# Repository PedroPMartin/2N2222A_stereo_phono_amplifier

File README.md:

2N2222A Stereo Phono Amplifier
=======
Based on [Hans Polak and Ivey's](https://www.diyaudio.com/community/threads/2n2222a-phono-preamp.158918/post-6392737) design. <br>
Thanks for Hans Polak and Ivey.

This design is similar but uses LM317 and no Zener diode

BOM <br>
Reference(s): Value <br>
C1, C2, C8, C9, C101, C102: 330uF /50V <br>
C3, C103	6n8 <br>
C4, C104	22n <br>
C5, C7, C105:	47uF / 50V <br>
C6, C106:	1uF/50V non electrolytic <br>
C11,C111: 3p3 <br>
J1, J3	TerminalBlock:TerminalBlock_bornier-3_P5.08mm  <br>
J2	TerminalBlock:TerminalBlock_bornier-2_P5.08mm  <br>
Q1, Q2, Q3, Q101, Q102, Q103:	2N2222A <br>
R1, R101:	150 Ohm <br>
R2, R9, R102, R109:	1K8 <br>
R3, R103:	8K2 <br>
R4, R8, R104, R108:	100 <br>
R5, R105:	12K <br>
R6, R106:	270K <br>
R7, R107:	6K <br>
R10, R110:	1K <br>
R12, R112:	47K <br>
R13, R113:	4K7 <br>
R14, R114:	10K <br>
R11: 220 <br>
R15:	3K3  <br>
U1:	LM317_TO-220 <cr>

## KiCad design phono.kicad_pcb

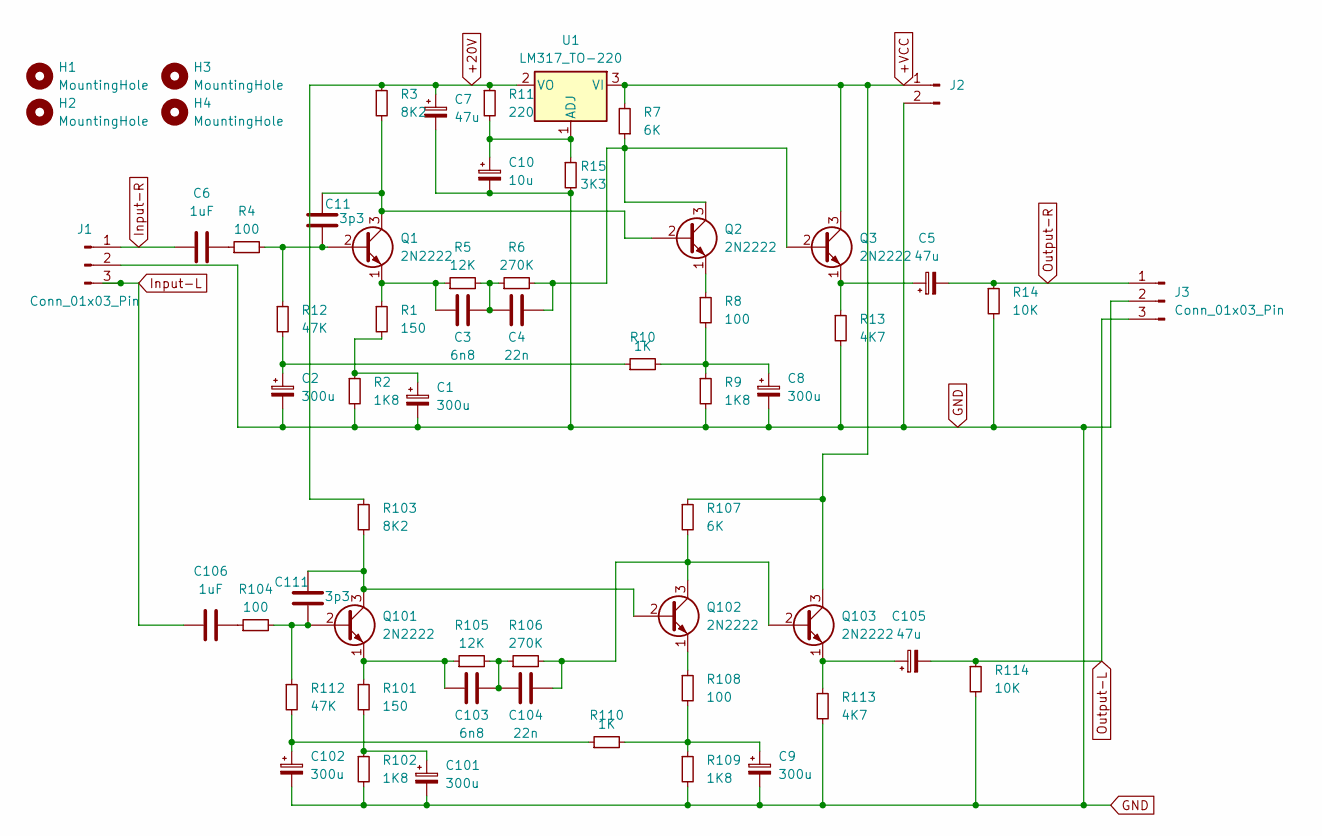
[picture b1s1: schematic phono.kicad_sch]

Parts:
C1, C2, C8, C9, C101, C102: 300u; CP_Radial_D10.0mm_P5.00mm
C3, C103: 6n8; C_Axial_L3.8mm_D2.6mm_P10.00mm_Horizontal
C4, C104: 22n; C_Axial_L3.8mm_D2.6mm_P10.00mm_Horizontal
C5, C7, C105: 47u; CP_Radial_D10.0mm_P5.00mm
C6, C106: 1uF; C_Axial_L3.8mm_D2.6mm_P10.00mm_Horizontal
C10: 10u; CP_Radial_D5.0mm_P2.00mm
C11, C111: 3p3; C_Disc_D3.0mm_W2.0mm_P2.50mm
H1, H2, H3, H4: MountingHole; MountingHole_3.2mm_M3
J1, J3: Conn_01x03_Pin; TerminalBlock_bornier-3_P5.08mm
J2: Conn_01x02_Pin; TerminalBlock_bornier-2_P5.08mm
Q1, Q2, Q3, Q101, Q102, Q103: 2N2222; TO-39-3
R1, R101: 150; R_Axial_DIN0207_L6.3mm_D2.5mm_P10.16mm_Horizontal
R2, R9, R102, R109: 1K8; R_Axial_DIN0207_L6.3mm_D2.5mm_P10.16mm_Horizontal
R3, R103: 8K2; R_Axial_DIN0207_L6.3mm_D2.5mm_P10.16mm_Horizontal
R4, R8, R104, R108: 100; R_Axial_DIN0207_L6.3mm_D2.5mm_P10.16mm_Horizontal
R5, R105: 12K; R_Axial_DIN0207_L6.3mm_D2.5mm_P10.16mm_Horizontal
R6, R106: 270K; R_Axial_DIN0207_L6.3mm_D2.5mm_P10.16mm_Horizontal
R7, R107: 6K; R_Axial_DIN0207_L6.3mm_D2.5mm_P10.16mm_Horizontal
R10, R110: 1K; R_Axial_DIN0207_L6.3mm_D2.5mm_P10.16mm_Horizontal
R11: 220; R_Axial_DIN0207_L6.3mm_D2.5mm_P10.16mm_Horizontal
R12, R112: 47K; R_Axial_DIN0207_L6.3mm_D2.5mm_P10.16mm_Horizontal
R13, R113: 4K7; R_Axial_DIN0207_L6.3mm_D2.5mm_P10.16mm_Horizontal
R14, R114: 10K; R_Axial_DIN0207_L6.3mm_D2.5mm_P10.16mm_Horizontal
R15: 3K3; R_Axial_DIN0207_L6.3mm_D2.5mm_P10.16mm_Horizontal
U1: LM317_TO-220; TO-220-3_Vertical

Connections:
+20V: C7.1, R3.1, R11.1, R103.1, U1.2 (VO)
+VCC: J2.1, Q3.3 (C), Q103.3 (C), R7.2, R107.1, U1.3 (VI)
GND: C1.2, C2.2, C7.2, C8.2, C9.2, C10.2, C101.2, C102.2, J1.2, J2.2, J3.2, R2.2, R9.2, R13.2, R14.2, R15.2, R102.2, R109.2, R113.2, R114.2
Input-L: C106.1, J1.3
Input-R: C6.1, J1.1
unnamed: C1.1, R1.2, R2.1
unnamed: C2.1, R10.1, R12.2
unnamed: C3.2, C4.1, R5.2, R6.1
unnamed: C6.2, R4.1
unnamed: C8.1, R8.2, R9.1, R10.2
unnamed: C9.1, R108.2, R109.1, R110.2
unnamed: C101.1, R101.2, R102.1
unnamed: C102.1, R110.1, R112.2
unnamed: C103.2, C104.1, R105.2, R106.1
unnamed: C106.2, R104.1
unnamed: C11.2, Q1.2 (B), R4.2, R12.1
unnamed: C11.1, Q1.3 (C), Q2.2 (B), R3.2
unnamed: C3.1, Q1.1 (E), R1.1, R5.1
unnamed: C4.2, Q2.3 (C), Q3.2 (B), R6.2, R7.1
unnamed: Q2.1 (E), R8.1
unnamed: C5.1, Q3.1 (E), R13.1
unnamed: C111.2, Q101.2 (B), R104.2, R112.1
unnamed: C111.1, Q101.3 (C), Q102.2 (B), R103.2
unnamed: C103.1, Q101.1 (E), R101.1, R105.1
unnamed: C104.2, Q102.3 (C), Q103.2 (B), R106.2, R107.2
unnamed: Q102.1 (E), R108.1
unnamed: C105.1, Q103.1 (E), R113.1
unnamed: C10.1, R11.2, R15.1, U1.1 (ADJ)
Output-L: C105.2, J3.3, R114.1
Output-R: C5.2, J3.1, R14.1

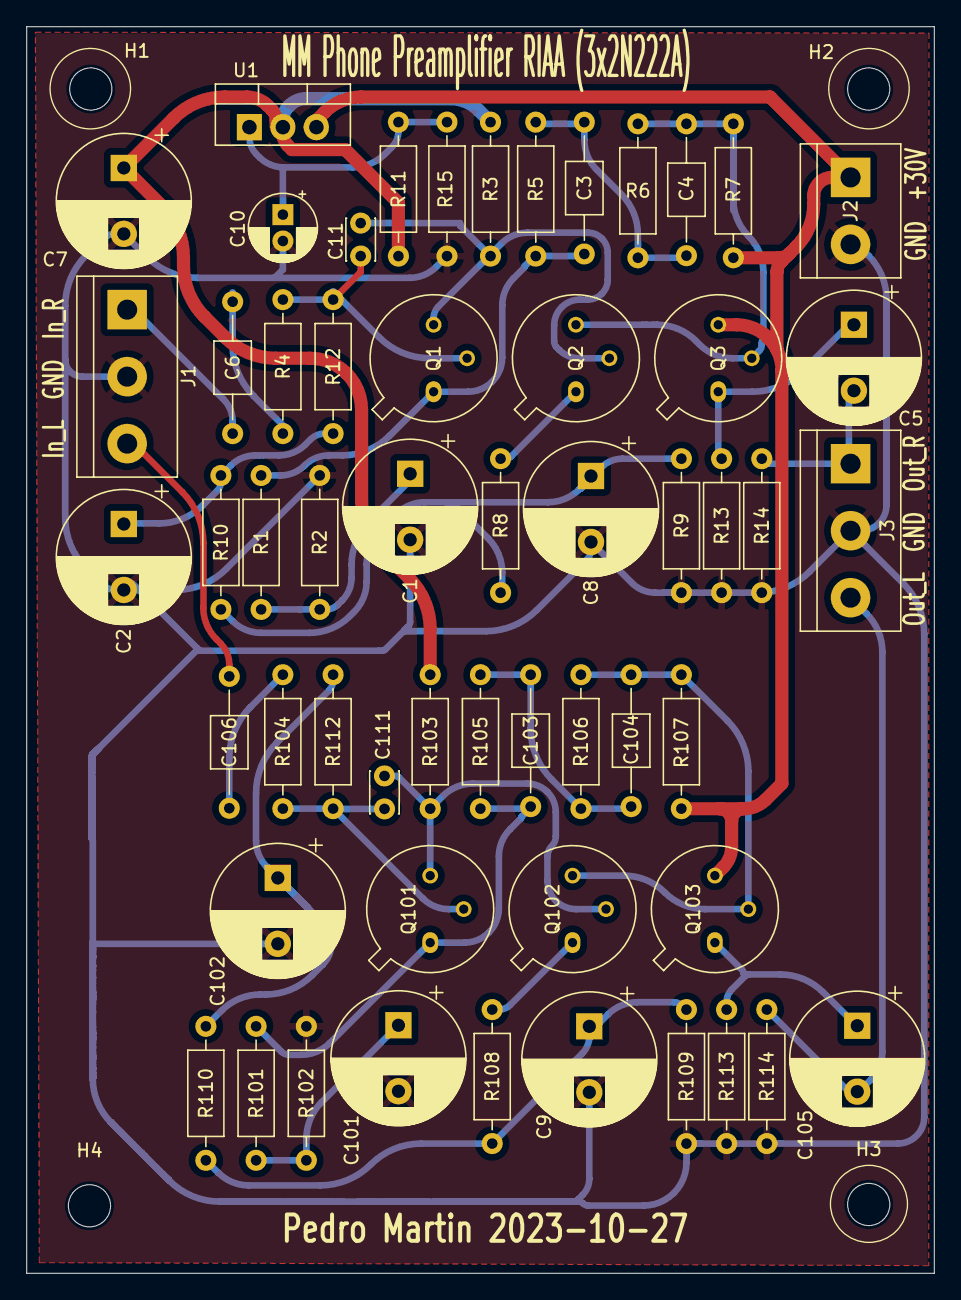
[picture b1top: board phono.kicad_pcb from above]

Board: 2 copper layers, 68.8 x 94.5 mm, 60 parts (0 on the bottom side), 30 nets.

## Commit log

2024-05-03 Update README.md
    added c11 capacitor to supress HF
2024-05-03 Add files via upload
    Esquema y placa actualizados para uso con Kicad 8
